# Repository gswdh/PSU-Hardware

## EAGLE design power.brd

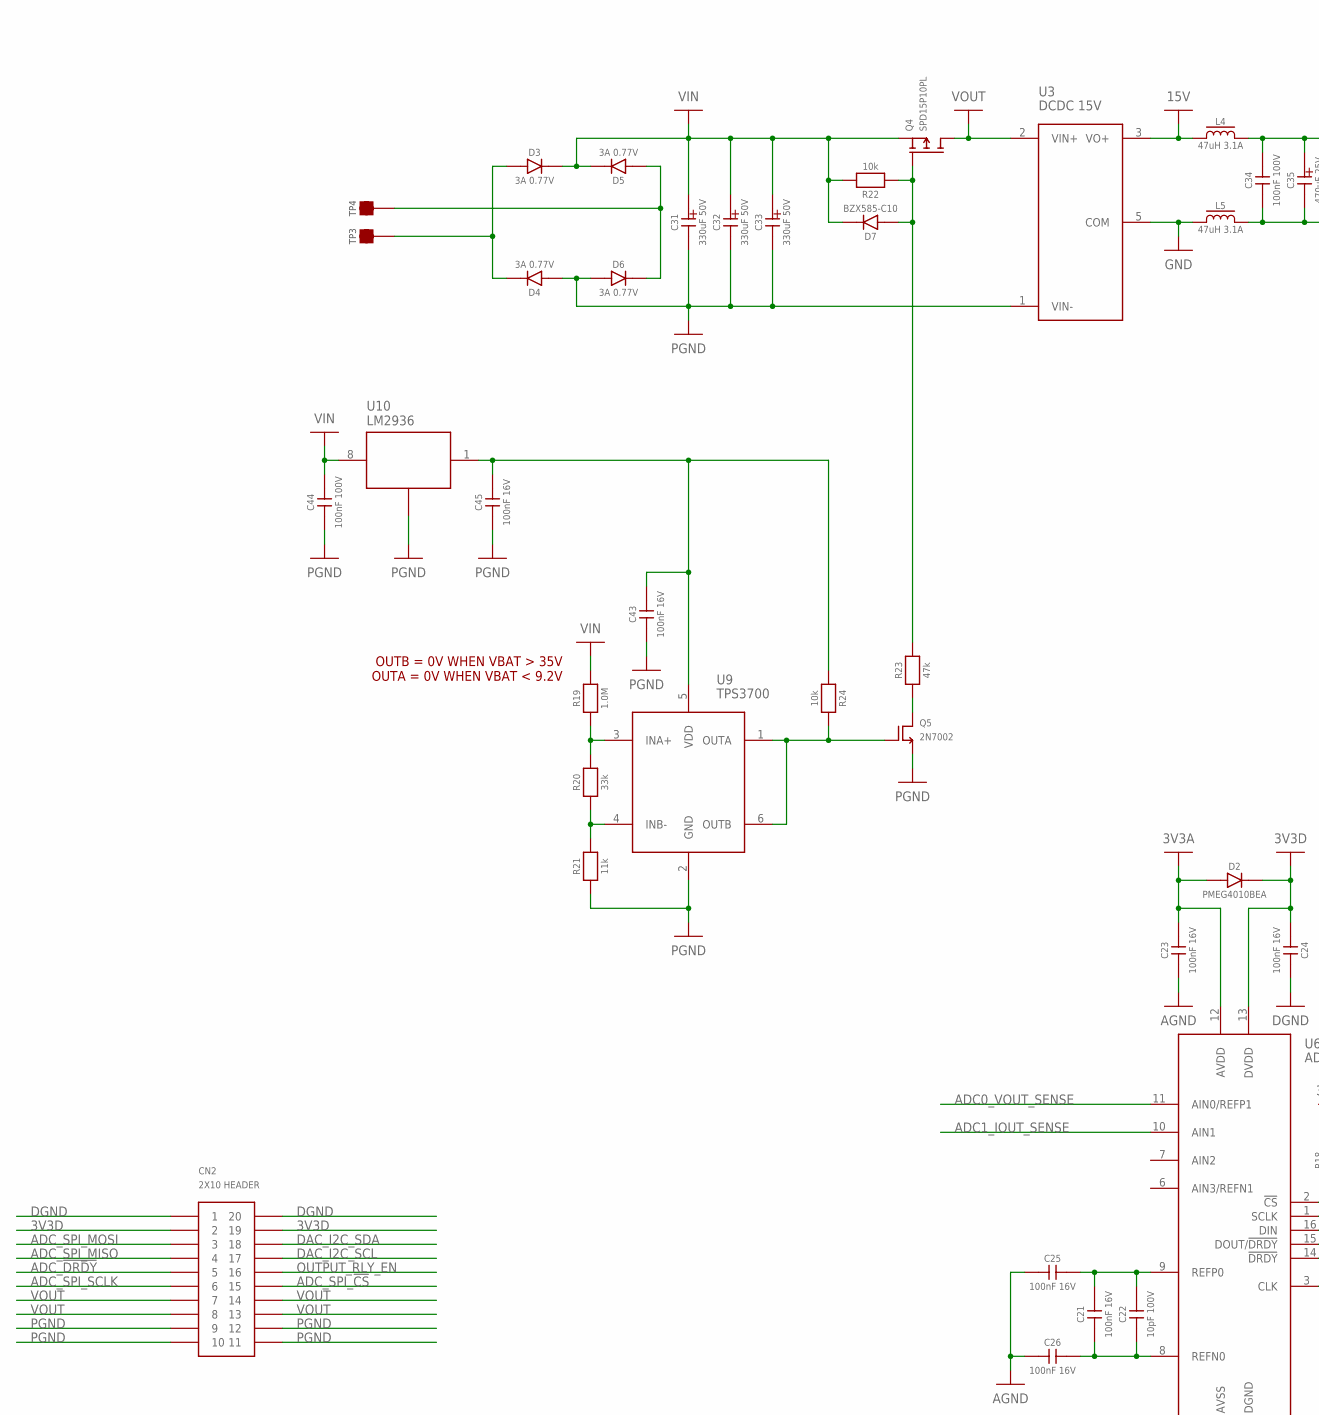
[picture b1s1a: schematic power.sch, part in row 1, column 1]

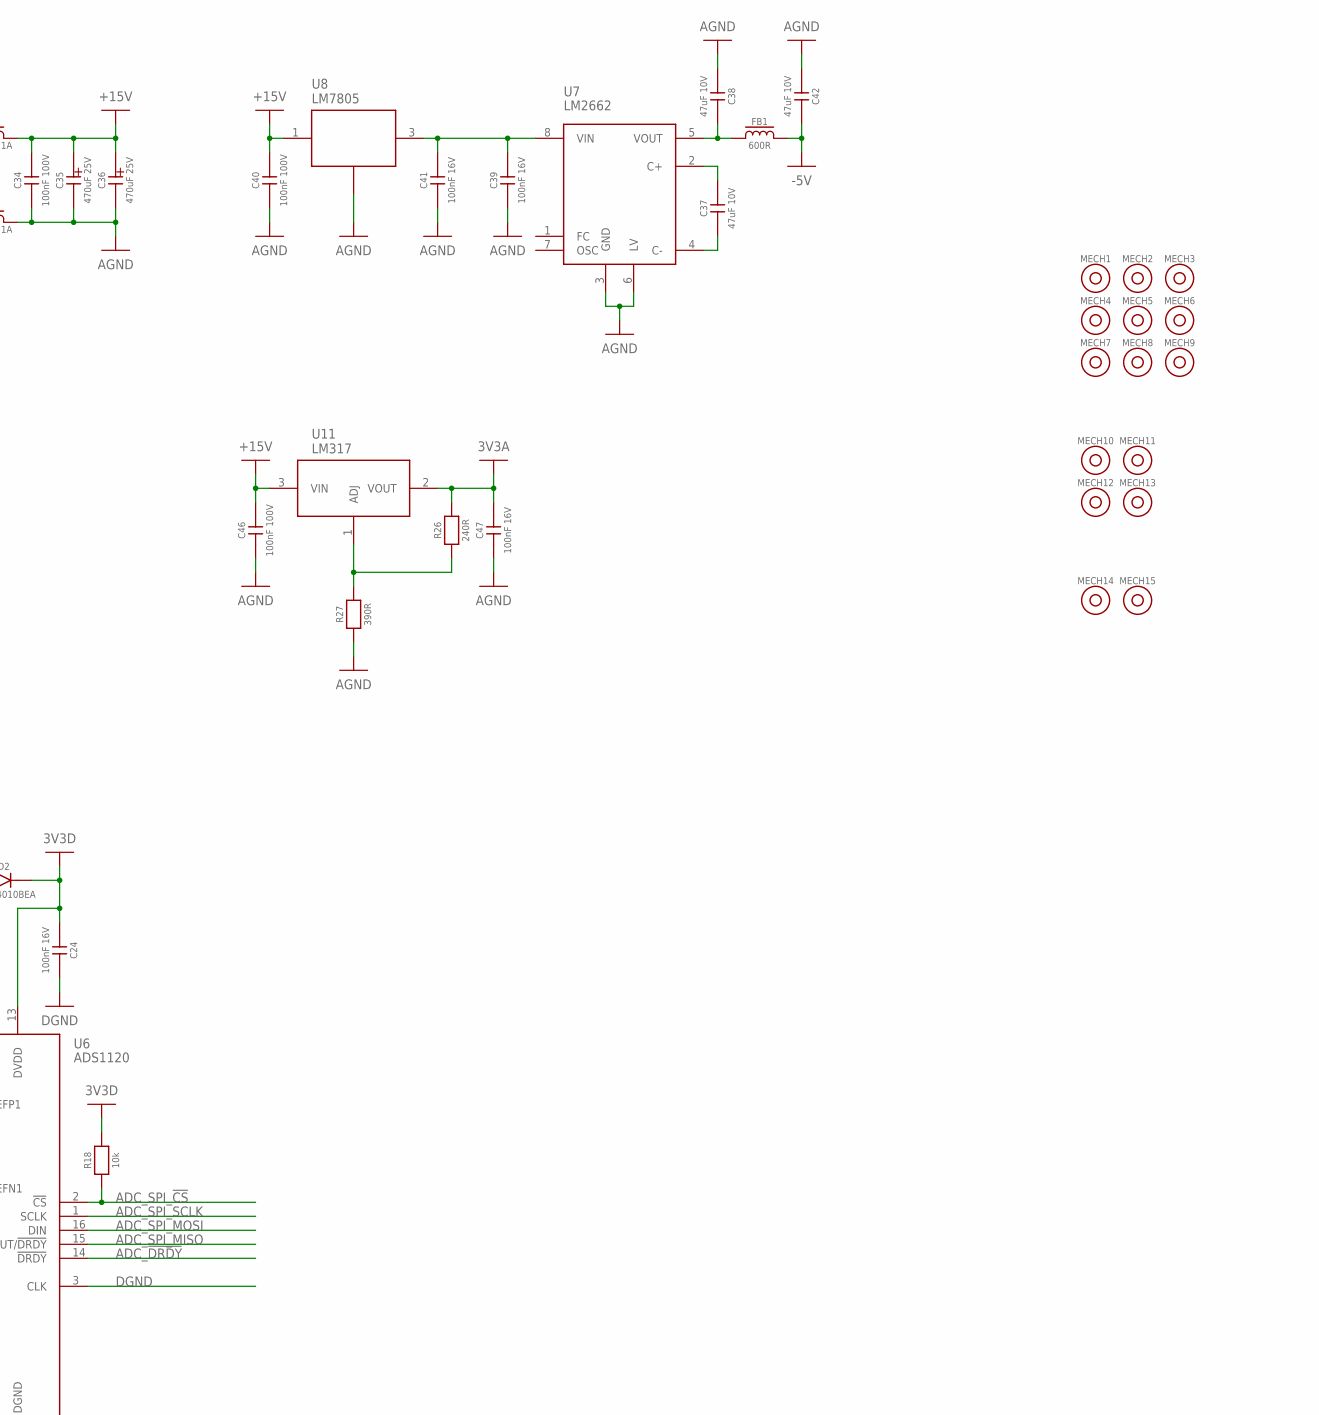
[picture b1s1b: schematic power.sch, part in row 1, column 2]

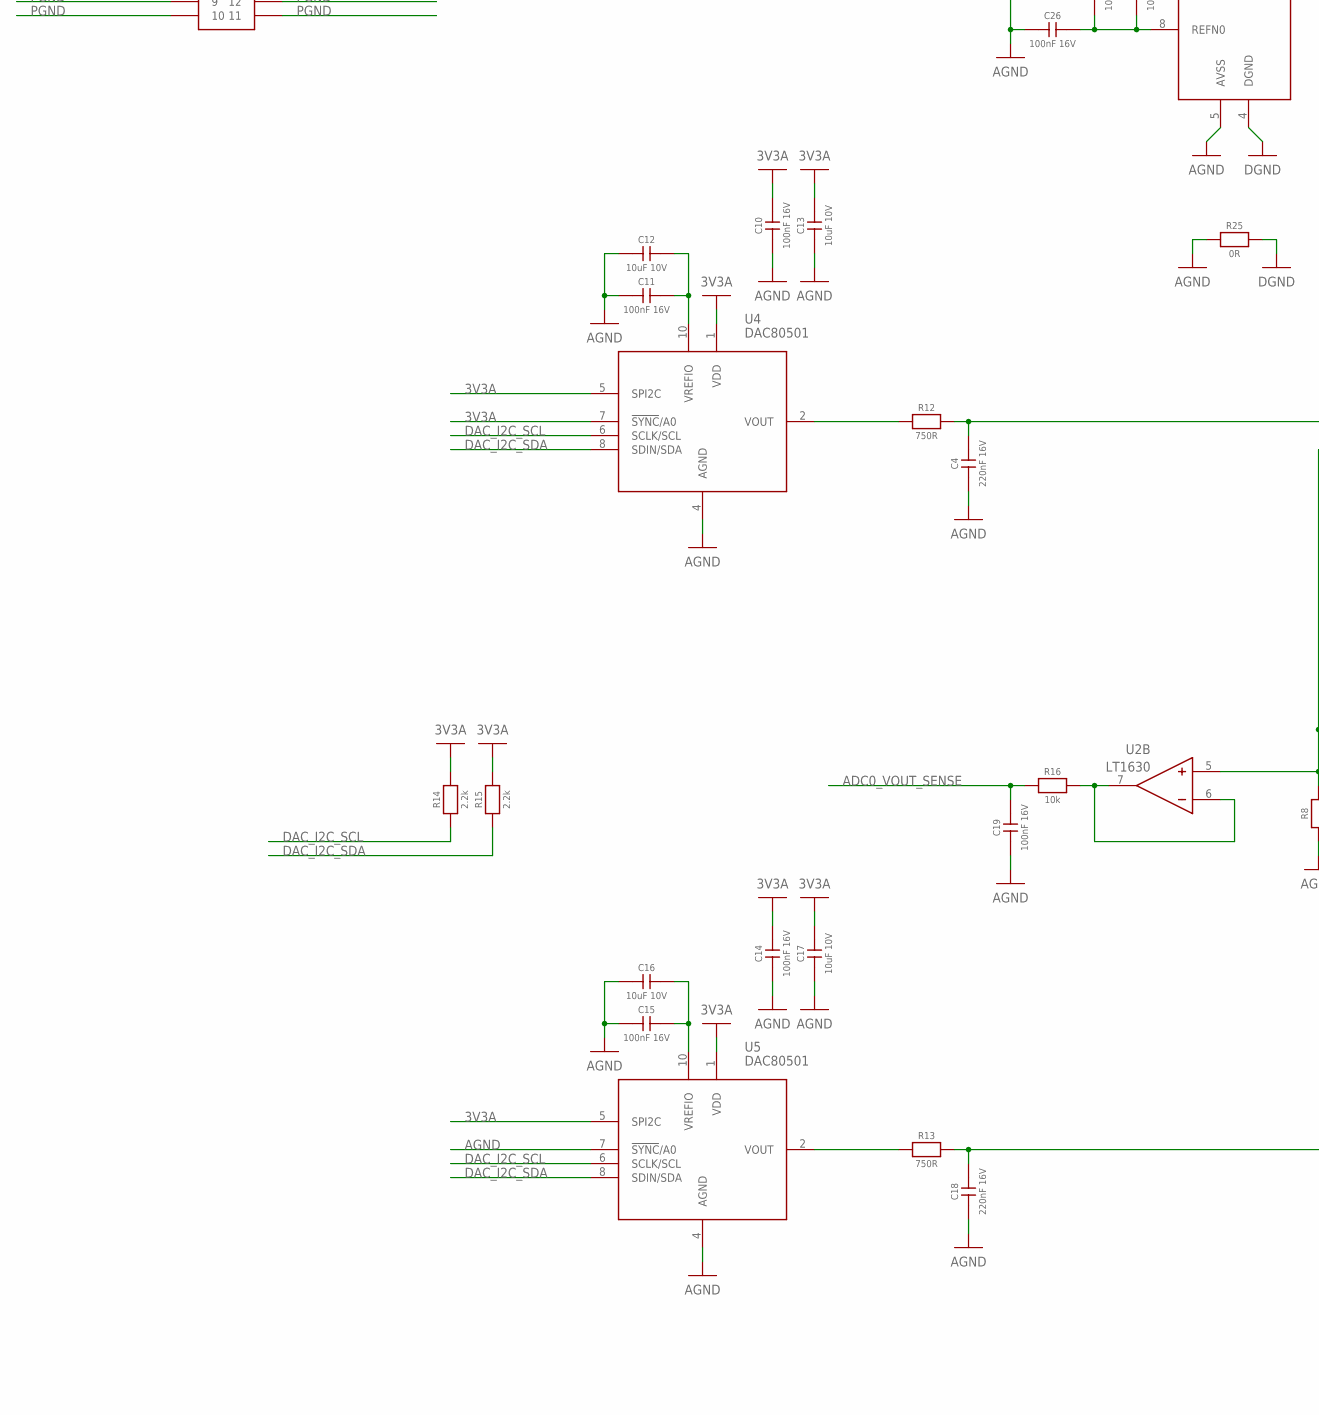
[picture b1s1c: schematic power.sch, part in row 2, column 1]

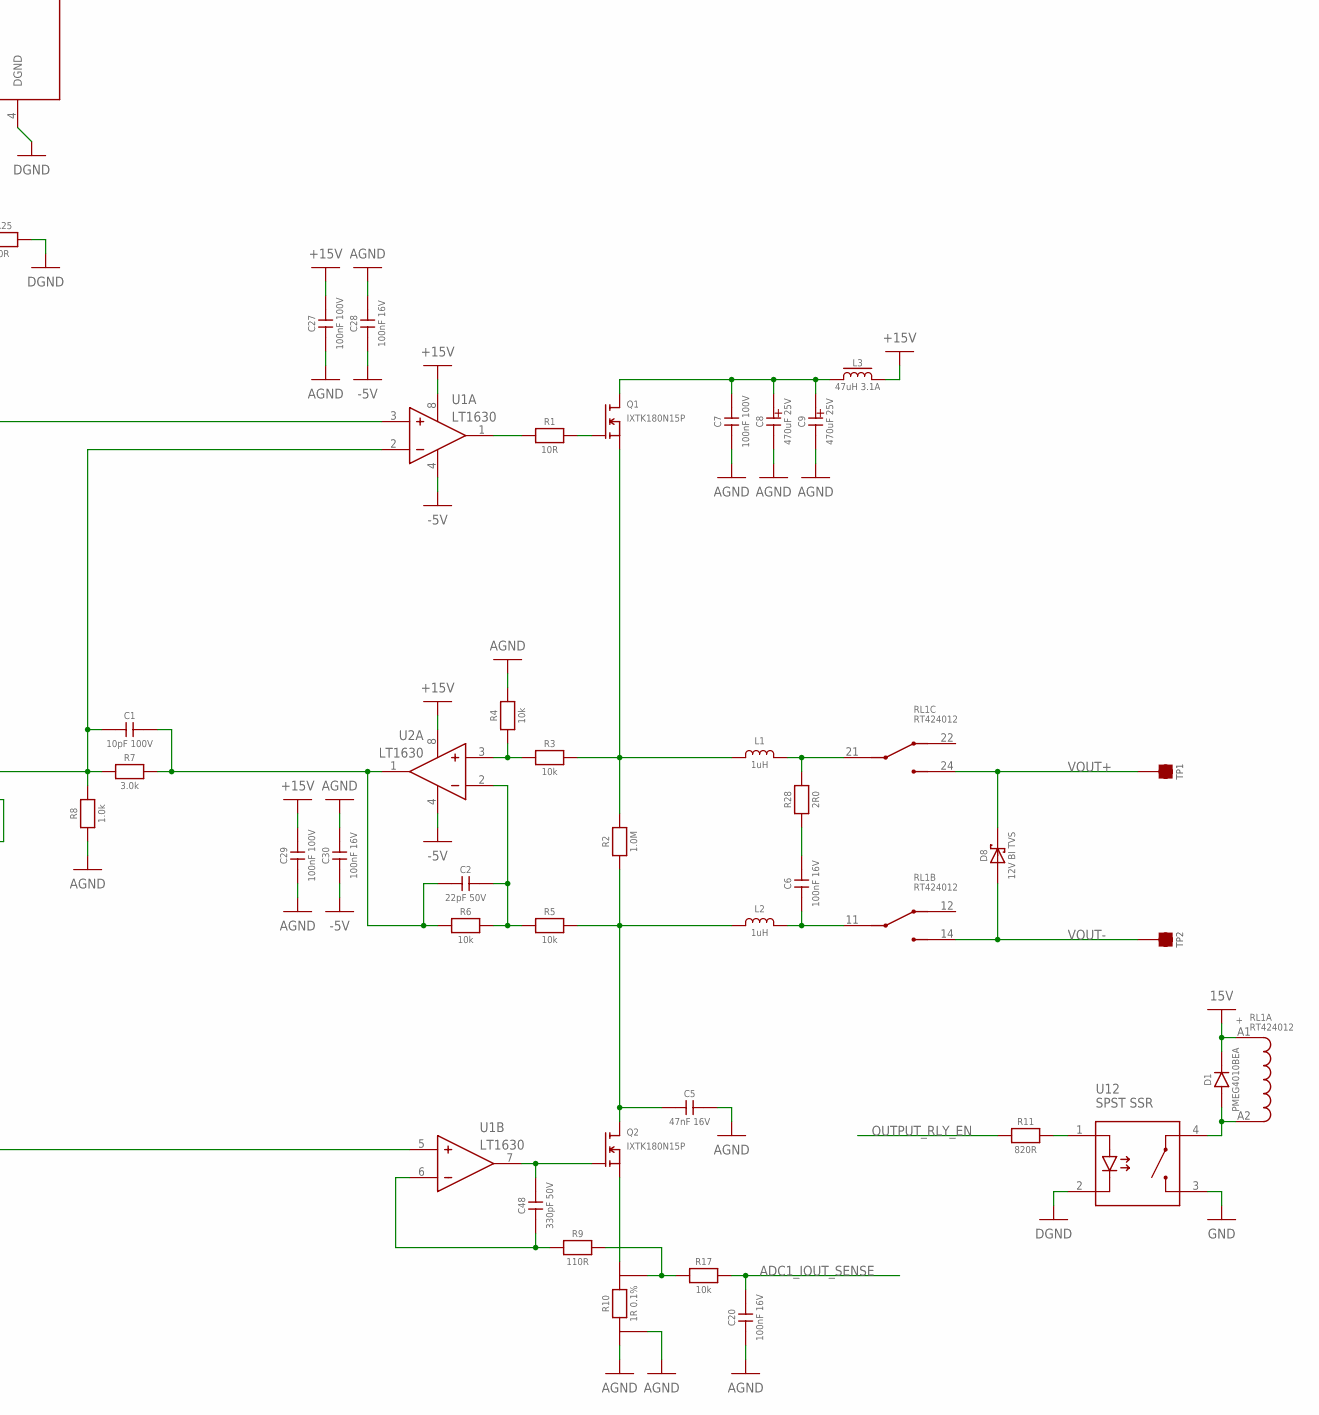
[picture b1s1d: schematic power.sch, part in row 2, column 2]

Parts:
C1, C22: 10pF 100V; 0603
C2: 22pF 50V; 0603
C4, C18: 220nF 16V; 0603
C5: 47nF 16V; 0603
C6, C10, C11, C14, C15, C19, C20, C21, C23, C24, C25, C26, C28, C30, C39, C41, C43, C45, C47: 100nF 16V; 0603
C7, C27, C29, C34, C40, C44, C46: 100nF 100V; 0603
C8, C9, C35, C36: 470uF 25V; 10MM_RADIAL_5MM_PITCH
C12, C13, C16, C17: 10uF 10V; 0603
C31, C32, C33: 330uF 50V; 10MM_RADIAL_5MM_PITCH
C37, C38, C42: 47uF 10V; 1206
C48: 330pF 50V; 0603
CN2: 2X10 HEADER; 2X10PIN_HEADER
D1, D2: PMEG4010BEA; SOD-323
D3, D4, D5, D6: 3A 0.77V; SOD128
D7: BZX585-C10; SOD_523
D8: 12V BI TVS; DO214AC
FB1: 600R; 0603
L1, L2: 1uH; DIY_10X13MM_INDUCTOR
L3, L4, L5: 47uH 3.1A; SRR1210
MECH1, MECH2, MECH3, MECH4, MECH5, MECH6, MECH7, MECH8, MECH9, MECH10, MECH11, MECH12, MECH13, MECH14, MECH15: 6mm x 3mm; MOUNTHOLE_6X3
Q1, Q2: IXTK180N15P; TO264F
Q4: SPD15P10PL; TO252
Q5: 2N7002; SOT23-3
R1: 10R; 0603
R2, R19: 1.0M; 0603
R3, R4, R5, R6, R16, R17, R18, R22, R24: 10k; 0603
R7: 3.0k; 0603
R8: 1.0k; 0603
R9: 110R; 0603
R10: 1R 0.1%; 2512_4WIRE
R11: 820R; 0603
R12, R13: 750R; 0603
R14, R15: 2.2k; 0603
R20: 33k; 0603
R21: 11k; 0603
R23: 47k; 0603
R25: 0R; 0603
R26: 240R; 0603
R27: 390R; 0603
R28: 2R0; 1206
RL1: RT424012; 30MMDPDTRELAY
TP1, TP2, TP3, TP4: TEST_POINT_SQUARE; OSPREY_HSS_PAD
U1, U2: LT1630; SO8
U3: DCDC 15V; PDQE10
U4, U5: DAC80501; VSSOP10
U6: ADS1120; TSSOP16
U7: LM2662; SO8
U8: LM7805; TO220
U9: TPS3700; SOT23-6
U10: LM2936; SO8
U11: LM317; TO220
U12: SPST SSR; CPC1002N

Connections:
3V3A: C10.2, C13.2, C14.2, C17.2, C23.2, C47.2, D2.A, R14.2, R15.2, R26.2, U4.1 (VDD), U4.5 (SPI2C), U4.7 (!SYNC!/A0), U5.1 (VDD), U5.5 (SPI2C), U6.12 (AVDD), U11.2 (VOUT)
3V3D: C24.1, CN2.2, CN2.19, D2.K, R18.2, U6.13 (DVDD)
15V: D1.K, L4.1, RL1.A1, U3.3 (VO+)
+15V: C27.2, C29.2, C34.2, C35.2 (A), C36.2 (A), C40.2, C46.2, L3.2, L4.2, U1.8 (V+), U2.8 (V+), U8.1 (VIN), U11.3 (VIN)
-5V: C28.1, C30.1, C42.2, FB1.2, U1.4 (V-), U2.4 (V-)
ADC0_VOUT_SENSE: C19.2, R16.1, U6.11 (AIN0/REFP1)
ADC1_IOUT_SENSE: C20.2, R17.2, U6.10 (AIN1)
ADC_!DRDY: CN2.5, U6.14 (!DRDY)
ADC_SPI_!CS: CN2.15, R18.1, U6.2 (!CS)
ADC_SPI_MISO: CN2.4, U6.15 (DOUT/!DRDY)
ADC_SPI_MOSI: CN2.3, U6.16 (DIN)
ADC_SPI_SCLK: CN2.6, U6.1 (SCLK)
AGND: C4.1, C5.2, C7.1, C8.1 (K), C9.1 (K), C10.1, C11.1, C12.1, C13.1, C14.1, C15.1, C16.1, C17.1, C18.1, C19.1, C20.1, C23.1, C25.1, C26.1, C27.1, C28.2, C29.1, C30.2, C34.1, C35.1 (K), C36.1 (K), C38.1, C39.1, C40.1, C41.1, C42.1, C46.1, C47.1, L5.2, R4.2, R8.1, R10.1 (E1), R10.2 (I1), R25.1, R27.1, U4.4 (AGND), U5.4 (AGND), U5.7 (!SYNC!/A0), U6.5 (AVSS), U7.3 (GND), U7.6 (LV), U8.2 (GND)
DAC_I2C_SCL: CN2.17, R14.1, U4.6 (SCLK/SCL), U5.6 (SCLK/SCL)
DAC_I2C_SDA: CN2.18, R15.1, U4.8 (SDIN/SDA), U5.8 (SDIN/SDA)
DGND: C24.2, CN2.1, CN2.20, R25.2, U6.3 (CLK), U6.4 (DGND), U12.2 (LED_K)
GND: L5.1, U3.5 (COM), U12.3 (SW2)
unnamed: R1.1, U1.1 (OUT)
unnamed: Q1.1 (G), R1.2
unnamed: L1.1, Q1.3 (S), R2.2, R3.2
unnamed: C5.1, L2.1, Q2.2 (D), R2.1, R5.2
unnamed: R3.1, R4.1, U2.3 (+)
unnamed: C2.2, R5.1, R6.2, U2.2 (-)
unnamed: C1.2, C2.1, R6.1, R7.2, U2.1 (OUT)
unnamed: R16.2, U2.6 (-), U2.7 (OUT)
unnamed: C48.2, Q2.1 (G), U1.7 (OUT)
unnamed: C4.2, R12.2, U1.3 (+)
unnamed: C48.1, R9.1, U1.6 (-)
unnamed: L1.2, R28.2, RL1.21 (1)
unnamed: R11.2, U12.1 (LED_A)
unnamed: C6.1, L2.2, RL1.11 (1)
unnamed: R26.1, R27.2, U11.1 (ADJ)
unnamed: C21.2, C22.2, C25.2, U6.9 (REFP0)
unnamed: C7.2, C8.2 (A), C9.2 (A), L3.1, Q1.2 (D)
unnamed: C18.2, R13.2, U1.5 (+)
unnamed: D1.A, RL1.A2, U12.4 (SW1)
unnamed: C11.2, C12.2, U4.10 (VREFIO)
unnamed: R12.1, U4.2 (VOUT)
unnamed: C15.2, C16.2, U5.10 (VREFIO)
unnamed: R13.1, U5.2 (VOUT)
unnamed: C21.1, C22.1, C26.2, U6.8 (REFN0)
unnamed: C43.2, C45.2, R24.1, U9.5 (VDD), U10.1 (VOUT)
unnamed: D5.A, D6.K, TP4.1
unnamed: D3.A, D4.K, TP3.1
unnamed: C6.2, R28.1
unnamed: Q2.3 (S), R10.4 (I2)
unnamed: C37.2, U7.2 (C+)
unnamed: C37.1, U7.4 (C-)
unnamed: C38.2, FB1.1, U7.5 (VOUT)
unnamed: C39.2, C41.2, U7.8 (VIN), U8.3 (VOUT)
unnamed: R19.1, R20.2, U9.3 (INA+)
unnamed: R20.1, R21.2, U9.4 (INB-)
unnamed: D7.A, Q4.1 (G), R22.1, R23.2
unnamed: Q5.2 (D), R23.1
unnamed: Q5.1 (G), R24.2, U9.1 (OUTA), U9.6 (OUTB)
unnamed: R9.2, R10.3 (E2), R17.1
unnamed: C1.1, R7.1, R8.2, U1.2 (-), U2.5 (+)
OUTPUT_RLY_EN: CN2.16, R11.1
PGND: C31.1 (K), C32.1 (K), C33.1 (K), C43.1, C44.1, C45.1, CN2.9, CN2.10, CN2.11, CN2.12, D4.A, D6.A, Q5.3 (S), R21.1, U3.1 (VIN-), U9.2 (GND), U10.2 (GND), U10.3 (GND), U10.6 (GND), U10.7 (GND)
VIN: C31.2 (A), C32.2 (A), C33.2 (A), C44.2, D3.K, D5.K, D7.K, Q4.3 (S), R19.2, R22.2, U10.8 (VIN)
VOUT: CN2.7, CN2.8, CN2.13, CN2.14, Q4.2 (D), U3.2 (VIN+)
VOUT+: D8.K, RL1.24 (3), TP1.1
VOUT-: D8.A, RL1.14 (3), TP2.1

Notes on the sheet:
OUTB = 0V WHEN VBAT > 35V OUTA = 0V WHEN VBAT < 9.2V

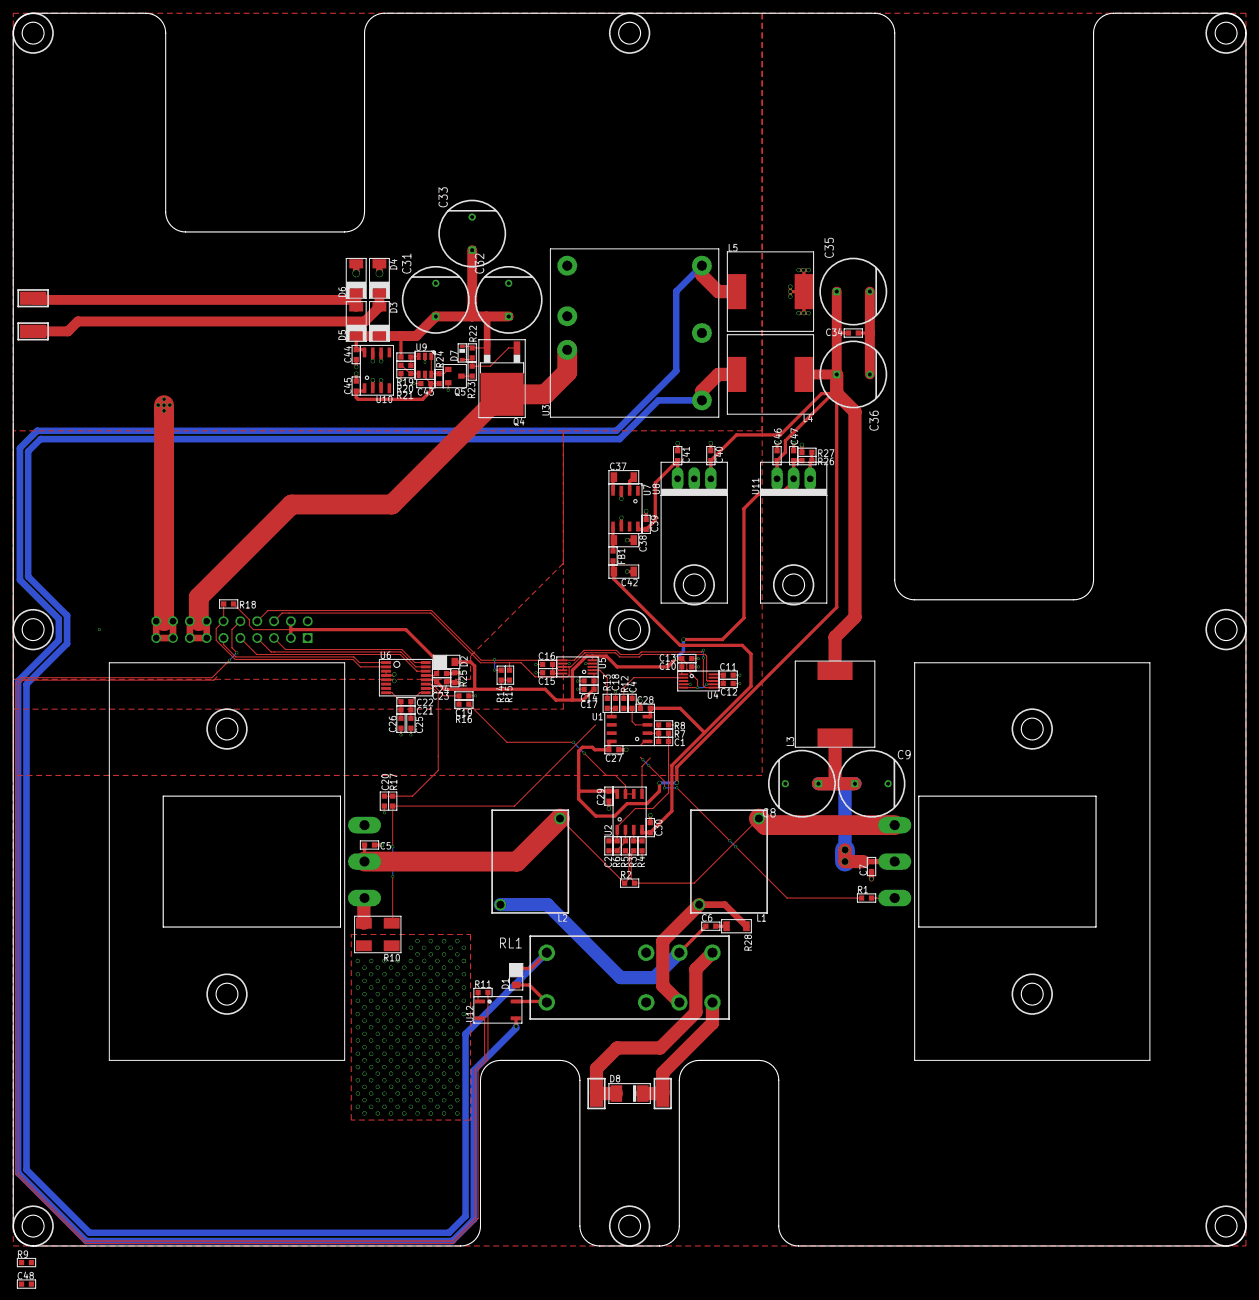
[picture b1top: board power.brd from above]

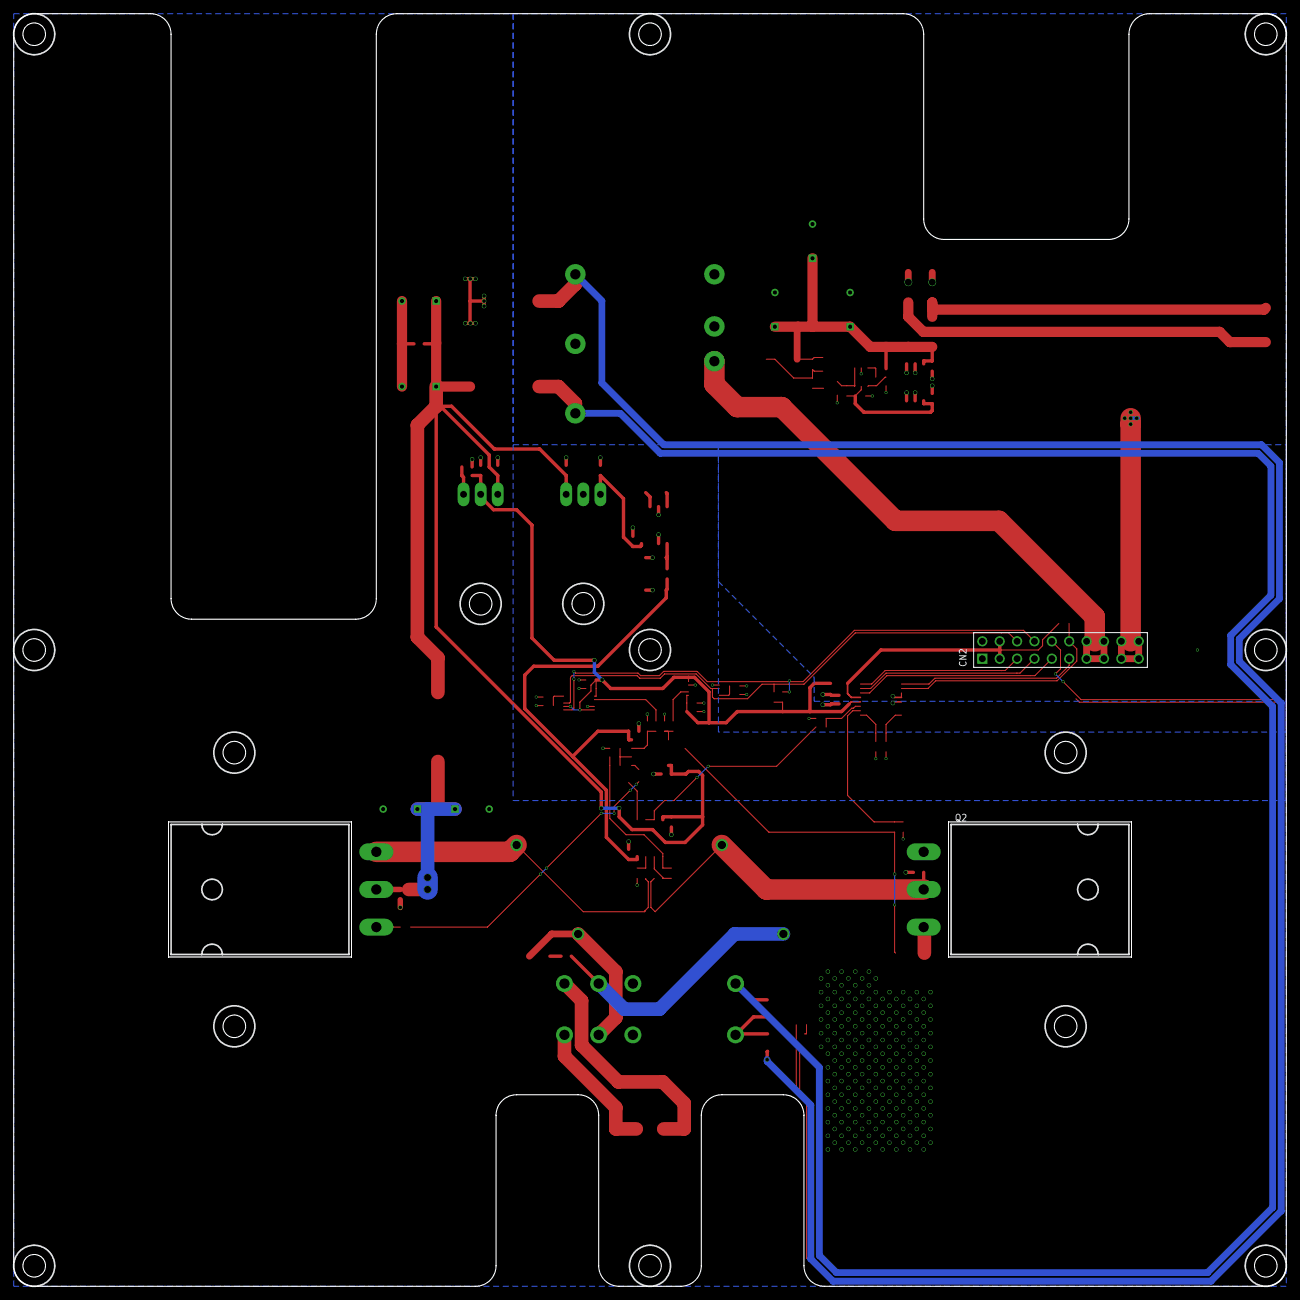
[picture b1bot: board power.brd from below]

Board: 4 copper layers, 186.0 x 186.0 mm, 126 parts (3 on the bottom side), 63 nets.

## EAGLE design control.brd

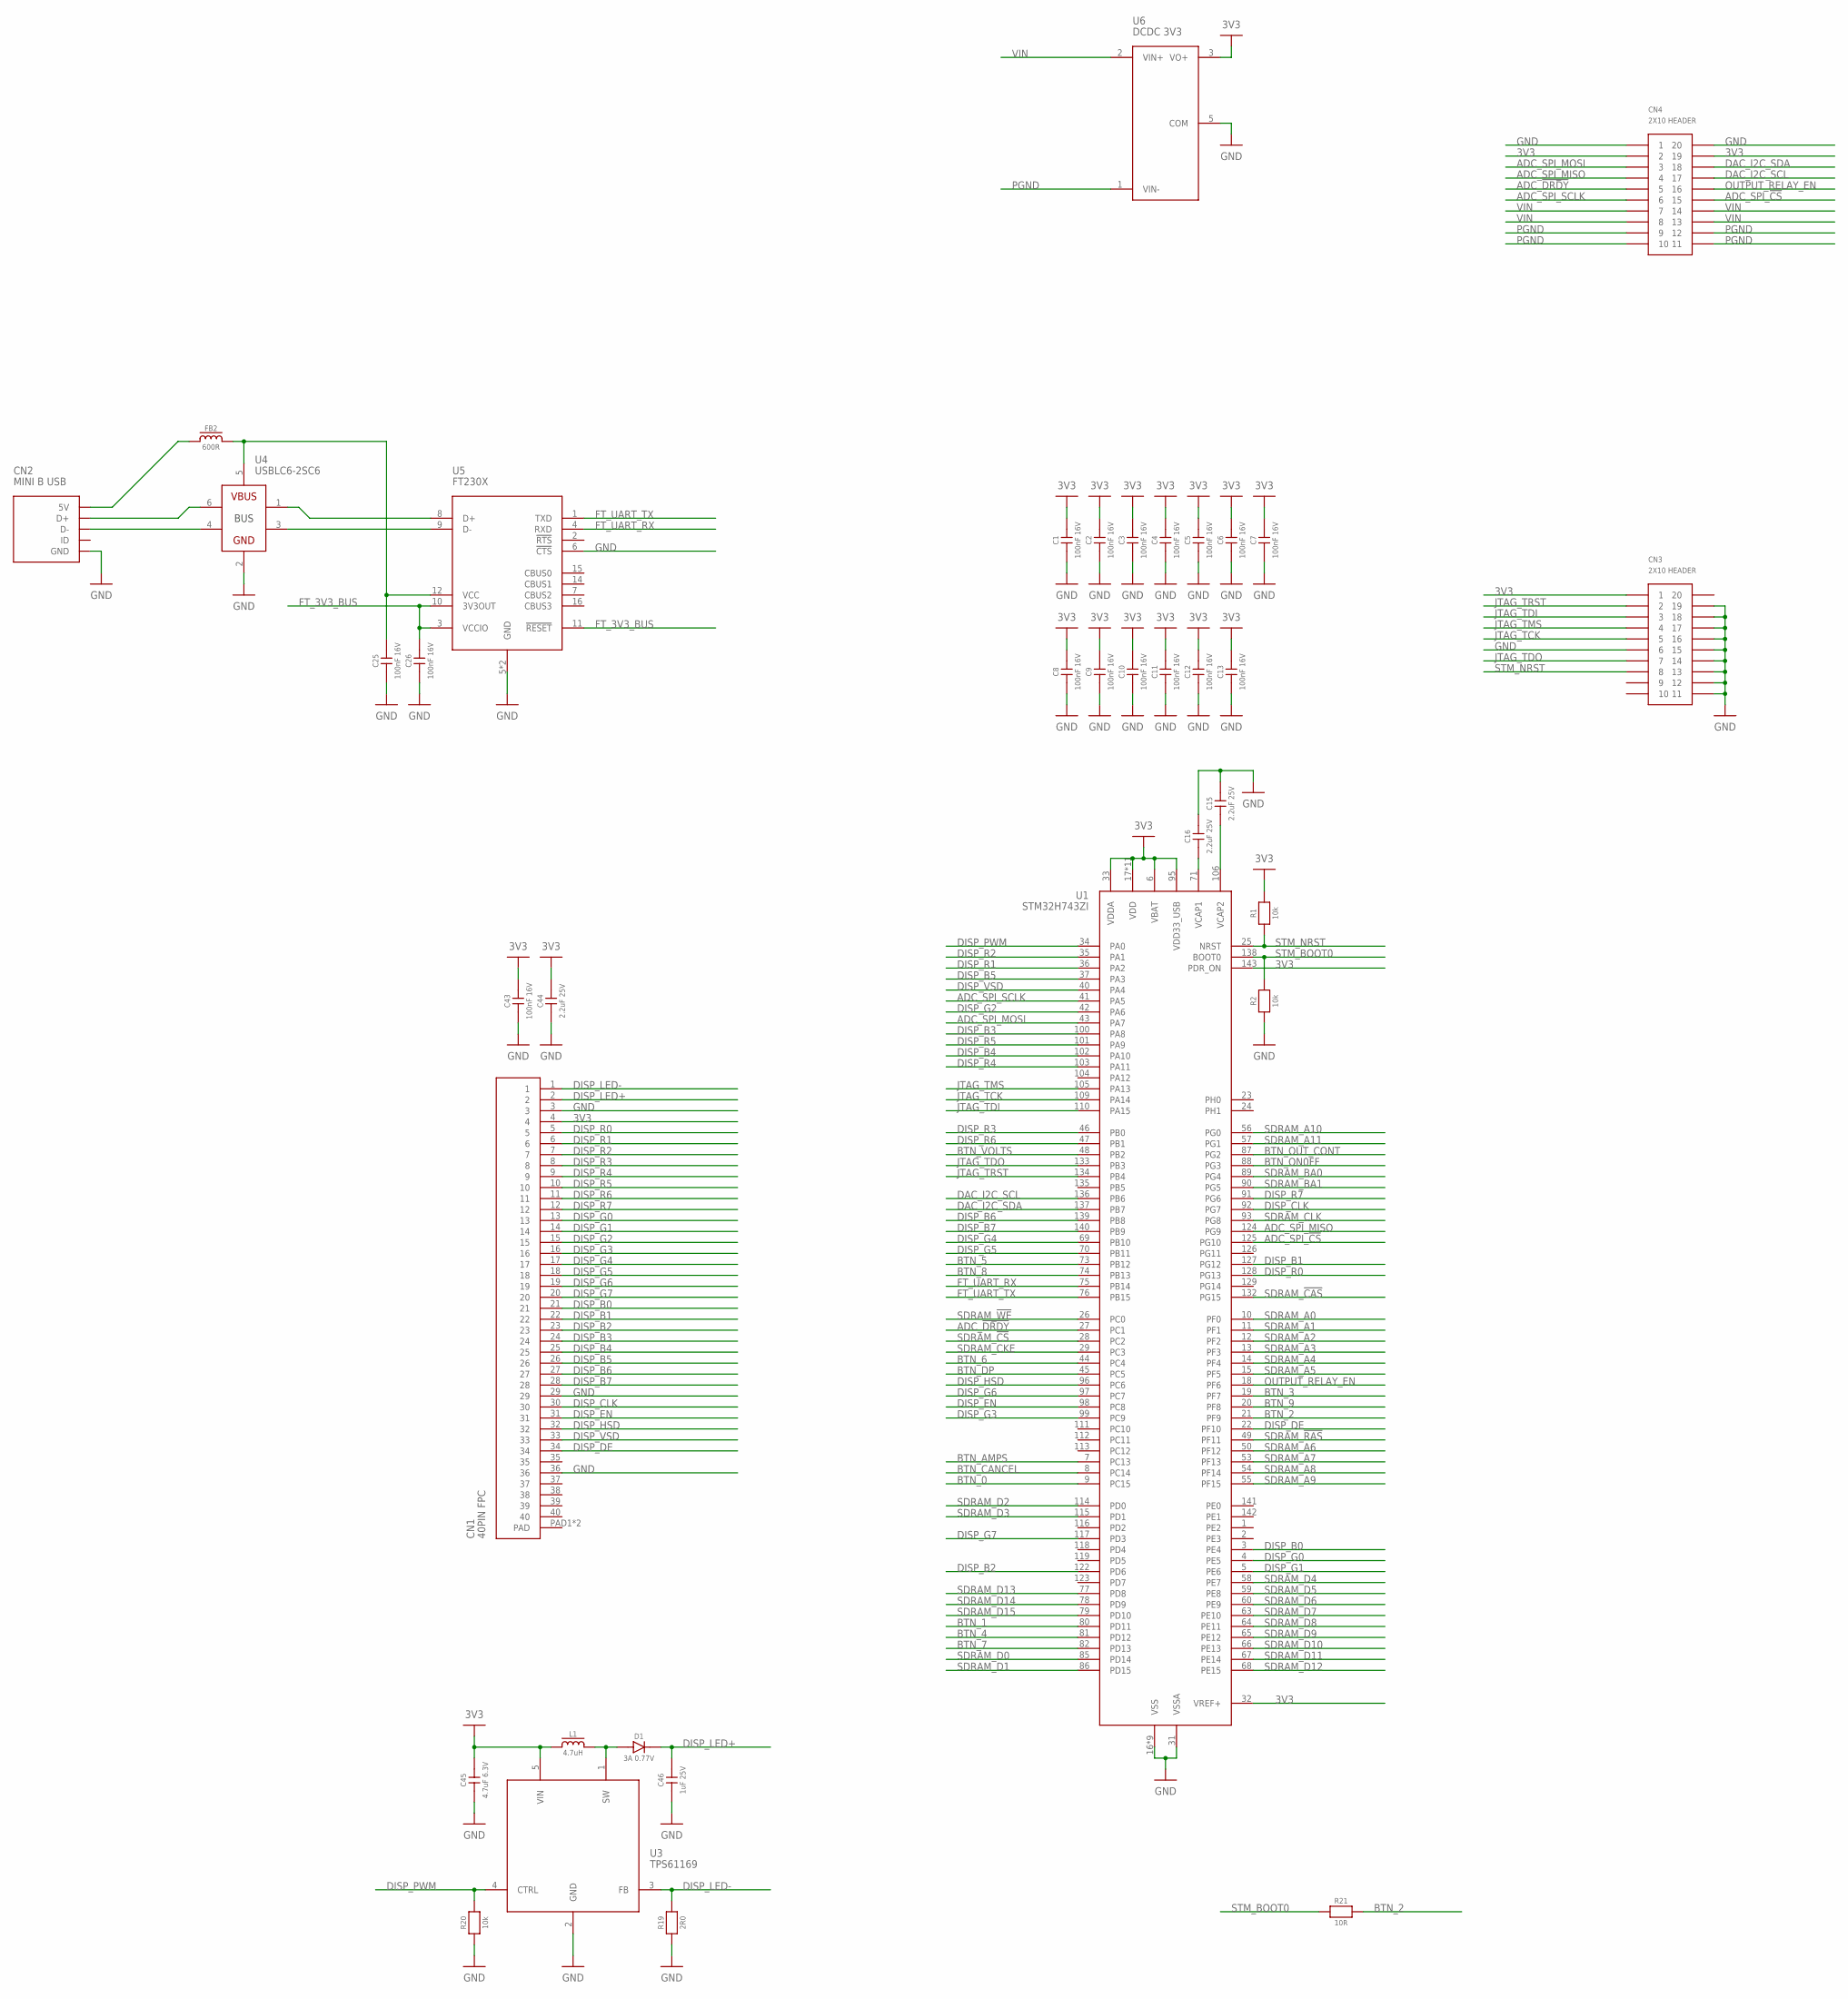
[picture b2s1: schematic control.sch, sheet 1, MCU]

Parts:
C1, C2, C3, C4, C5, C6, C7, C8, C9, C10, C11, C12, C13, C25, C26, C43: 100nF 16V; 0603
C15, C16, C44: 2.2uF 25V; 0603
C45: 4.7uF 6.3V; 0603
C46: 1uF 25V; 0603
CN1: 40PIN FPC; XF2M40151A
CN2: MINI B USB; MUSB-05-S-B-SM-A
CN3, CN4: 2X10 HEADER; 2X10PIN_HEADER
D1: 3A 0.77V; SOD128
FB2: 600R; 0603
L1: 4.7uH; SRN6045
R1, R2, R20: 10k; 0603
R19: 2R0; 1206
R21: 10R; 0603
U1: STM32H743ZI; QFP144
U3: TPS61169; SOT23-5
U4: USBLC6-2SC6; SOT23-6
U5: FT230X; SSOP16-4MM
U6: DCDC 3V3; PDQE10

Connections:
3V3: C1.2, C2.2, C3.2, C4.2, C5.2, C6.2, C7.2, C8.2, C9.2, C10.2, C11.2, C12.2, C13.2, C43.2, C44.2, C45.2, CN1.4, CN3.1, CN4.2, CN4.19, L1.1, R1.2, U1.6 (VBAT), U1.17 (VDD), U1.30 (VDD), U1.32 (VREF+), U1.33 (VDDA), U1.39 (VDD), U1.52 (VDD), U1.62 (VDD), U1.72 (VDD), U1.84 (VDD), U1.95 (VDD33_USB), U1.108 (VDD), U1.121 (VDD), U1.131 (VDD), U1.143 (PDR_ON), U1.144 (VDD), U3.5 (VIN), U6.3 (VO+); also elsewhere on the board
ADC_!DRDY: CN4.5, U1.27 (PC1)
ADC_SPI_!CS: CN4.15, U1.125 (PG10)
ADC_SPI_MISO: CN4.4, U1.124 (PG9)
ADC_SPI_MOSI: CN4.3, U1.43 (PA7)
ADC_SPI_SCLK: CN4.6, U1.41 (PA5)
BTN_0: U1.9 (PC15); also elsewhere on the board
BTN_1: U1.80 (PD11); also elsewhere on the board
BTN_2: R21.2, U1.21 (PF9); also elsewhere on the board
BTN_3: U1.19 (PF7); also elsewhere on the board
BTN_4: U1.81 (PD12); also elsewhere on the board
BTN_5: U1.73 (PB12); also elsewhere on the board
BTN_6: U1.44 (PC4); also elsewhere on the board
BTN_7: U1.82 (PD13); also elsewhere on the board
BTN_8: U1.74 (PB13); also elsewhere on the board
BTN_9: U1.20 (PF8); also elsewhere on the board
BTN_AMPS: U1.7 (PC13); also elsewhere on the board
BTN_CANCEL: U1.8 (PC14); also elsewhere on the board
BTN_DP: U1.45 (PC5); also elsewhere on the board
BTN_ON0FF: U1.88 (PG3); also elsewhere on the board
BTN_OUT_CONT: U1.87 (PG2); also elsewhere on the board
BTN_VOLTS: U1.48 (PB2); also elsewhere on the board
DAC_I2C_SCL: CN4.17, U1.136 (PB6)
DAC_I2C_SDA: CN4.18, U1.137 (PB7)
DISP_B0: CN1.21, U1.3 (PE4)
DISP_B1: CN1.22, U1.127 (PG12)
DISP_B2: CN1.23, U1.122 (PD6)
DISP_B3: CN1.24, U1.100 (PA8)
DISP_B4: CN1.25, U1.102 (PA10)
DISP_B5: CN1.26, U1.37 (PA3)
DISP_B6: CN1.27, U1.139 (PB8)
DISP_B7: CN1.28, U1.140 (PB9)
DISP_CLK: CN1.30, U1.92 (PG7)
DISP_DE: CN1.34, U1.22 (PF10)
DISP_EN: CN1.31, U1.98 (PC8)
DISP_G0: CN1.13, U1.4 (PE5)
DISP_G1: CN1.14, U1.5 (PE6)
DISP_G2: CN1.15, U1.42 (PA6)
DISP_G3: CN1.16, U1.99 (PC9)
DISP_G4: CN1.17, U1.69 (PB10)
DISP_G5: CN1.18, U1.70 (PB11)
DISP_G6: CN1.19, U1.97 (PC7)
DISP_G7: CN1.20, U1.117 (PD3)
DISP_HSD: CN1.32, U1.96 (PC6)
DISP_LED+: C46.2, CN1.2, D1.K
DISP_LED-: CN1.1, R19.2, U3.3 (FB)
DISP_PWM: R20.2, U1.34 (PA0), U3.4 (CTRL)
DISP_R0: CN1.5, U1.128 (PG13)
DISP_R1: CN1.6, U1.36 (PA2)
DISP_R2: CN1.7, U1.35 (PA1)
DISP_R3: CN1.8, U1.46 (PB0)
DISP_R4: CN1.9, U1.103 (PA11)
DISP_R5: CN1.10, U1.101 (PA9)
DISP_R6: CN1.11, U1.47 (PB1)
DISP_R7: CN1.12, U1.91 (PG6)
DISP_VSD: CN1.33, U1.40 (PA4)
FT_3V3_BUS: C26.2, U5.3 (VCCIO), U5.10 (3V3OUT), U5.11 (!RESET)
FT_UART_RX: U1.75 (PB14), U5.4 (RXD)
FT_UART_TX: U1.76 (PB15), U5.1 (TXD)
GND: C1.1, C2.1, C3.1, C4.1, C5.1, C6.1, C7.1, C8.1, C9.1, C10.1, C11.1, C12.1, C13.1, C15.2, C16.2, C25.1, C26.1, C43.1, C44.1, C45.1, C46.1, CN1.3, CN1.29, CN1.36, CN2.GND, CN2.SHIELD1 (GND), CN2.SHIELD2 (GND), CN2.SHIELD3 (GND), CN2.SHIELD4 (GND), CN3.6, CN3.11, CN3.12, CN3.13, CN3.14, CN3.15, CN3.16, CN3.17, CN3.18, CN3.19, CN4.1, CN4.20, R2.1, R19.1, R20.1, U1.16 (VSS), U1.31 (VSSA), U1.38 (VSS), U1.51 (VSS), U1.61 (VSS), U1.83 (VSS), U1.94 (VSS), U1.107 (VSS), U1.120 (VSS), U1.130 (VSS), U3.2 (GND), U4.2 (GND), U5.5 (GND), U5.6 (!CTS), U5.13 (GND), U6.5 (COM); also elsewhere on the board
JTAG_TCK: CN3.5, U1.109 (PA14)
JTAG_TDI: CN3.3, U1.110 (PA15)
JTAG_TDO: CN3.7, U1.133 (PB3)
JTAG_TMS: CN3.4, U1.105 (PA13)
JTAG_TRST: CN3.2, U1.134 (PB4)
unnamed: C16.1, U1.71 (VCAP1)
unnamed: C15.1, U1.106 (VCAP2)
unnamed: CN2.D-, U4.4 (D-OUT)
unnamed: CN2.D+, U4.6 (D+_OUT)
unnamed: U4.3 (D-_IN), U5.9 (D-)
unnamed: U4.1 (D+_IN), U5.8 (D+)
unnamed: CN2.VCC (5V), FB2.1
unnamed: C25.2, FB2.2, U4.5 (VBUS), U5.12 (VCC)
unnamed: D1.A, L1.2, U3.1 (SW)
OUTPUT_RELAY_EN: CN4.16, U1.18 (PF6)
PGND: CN4.9, CN4.10, CN4.11, CN4.12, U6.1 (VIN-)
SDRAM_!CAS: U1.132 (PG15)
SDRAM_!CS: U1.28 (PC2)
SDRAM_!RAS: U1.49 (PF11)
SDRAM_!WE: U1.26 (PC0)
SDRAM_A0: U1.10 (PF0)
SDRAM_A1: U1.11 (PF1)
SDRAM_A2: U1.12 (PF2)
SDRAM_A3: U1.13 (PF3)
SDRAM_A4: U1.14 (PF4)
SDRAM_A5: U1.15 (PF5)
SDRAM_A6: U1.50 (PF12)
SDRAM_A7: U1.53 (PF13)
SDRAM_A8: U1.54 (PF14)
SDRAM_A9: U1.55 (PF15)
SDRAM_A10: U1.56 (PG0)
SDRAM_A11: U1.57 (PG1)
SDRAM_BA0: U1.89 (PG4)
SDRAM_BA1: U1.90 (PG5)
SDRAM_CKE: U1.29 (PC3)
SDRAM_CLK: U1.93 (PG8)
SDRAM_D0: U1.85 (PD14)
SDRAM_D1: U1.86 (PD15)
SDRAM_D2: U1.114 (PD0)
SDRAM_D3: U1.115 (PD1)
SDRAM_D4: U1.58 (PE7)
SDRAM_D5: U1.59 (PE8)
SDRAM_D6: U1.60 (PE9)
SDRAM_D7: U1.63 (PE10)
SDRAM_D8: U1.64 (PE11)
SDRAM_D9: U1.65 (PE12)
SDRAM_D10: U1.66 (PE13)
SDRAM_D11: U1.67 (PE14)
SDRAM_D12: U1.68 (PE15)
SDRAM_D13: U1.77 (PD8)
SDRAM_D14: U1.78 (PD9)
SDRAM_D15: U1.79 (PD10)
STM_BOOT0: R2.2, R21.1, U1.138 (BOOT0)
STM_NRST: CN3.8, R1.1, U1.25 (NRST)
VIN: CN4.7, CN4.8, CN4.13, CN4.14, U6.2 (VIN+)

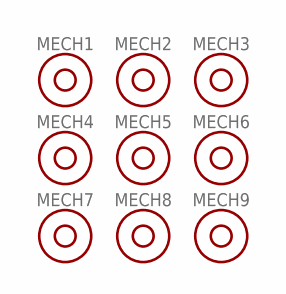
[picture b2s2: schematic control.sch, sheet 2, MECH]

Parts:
MECH1, MECH2, MECH3, MECH4, MECH5, MECH6, MECH7, MECH8, MECH9: 6mm x 3mm; MOUNTHOLE_6X3
